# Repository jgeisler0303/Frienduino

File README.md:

# The Frienduino
The Frienduino is an Arduino clone you can make for a friend once you have any kind of Arduino and some soldering skill.
The board is easy to make (single sided) and easy to solder (only through hole components).
It has everything to get started yet it is cheap and simple because it saves on stuff the novice doesn't need (separate power supply and 3.3V regulator).

IMHO, what made the Arduino so popular is its USB connectivity. This lowers the entry barrier to near zero.
No messing around with programmers, no legacy serial port required.
Alas, most of the many many Arduino clones out there lack this key feature.
I guess the reason for this is that, until now, all USB to serial adapters were not available as a through hole component, 
thus discouraging the novice to build a "true to the spirit" clone on their own.

It may seem odd at first to use a programmable micro controller just as a dumb USB to serial converter, but if you look at the price tag and consider it's the only way to get USB to serial as a through hole part it makes a lot of sense to me.
And not to me alone. The folks over at UNL Maker Club must have had a similar reasoning when they chose the 16F1454 as the USB adapter for their [Innovation Board](http://make.unl.edu/innovation-board/), an all SMD Arduino clone.

## Usage
Windows users will find the driver .inf file in this repository. If you connect your ready to use (firmware flashed) Frienduino to a USB port and Windows refuses to identify it as a virtual COM port, go the hardware section of your system configuration and manually update the driver. When asked for the new dirver file point to the inf file supplied in the repository.

Linux users should have no problem. The driver should be automatically installed. But maybe you will have trouble using the serial port created by the driver. In this case you will have to run the Arduino IDE as root or better create a rule to allow ordinary users to use the port (TODO: add link to advice on creating a USB rule file).

## Design
The schematic and PCB are a copy of the [Arduino Duemilanove](http://arduino.cc/en/pmwiki.php?n=Main/arduinoBoardDuemilanove) reference design modified to be a single sided layout using the 16F1454 as the USB adapter and striped off the external power supply. Reset button and ICSP header were moved for better accessability and less complicated routing respectively.

## Making
If you intend to have the Frienduino PCB made, there now is a ready to use gerber file in the repository. If you want the PCBs made by [http://www.seeedstudio.com](http://www.seeedstudio.com) you can even uses this [ready to order project](http://www.seeedstudio.com/service/WmUiIGK1).

For German hackers I have prepared a public [reichelt](http://www.reichelt.de/) shopping cart with all the parts needed [here](https://secure.reichelt.de/index.html?&ACTION=20&AWKID=1013176&PROVID=2084). It totals to 7.78EUR.

## Flashing the PIC 16F1454
The pre-compiled firmware to turn the PIC 16F1454 into a serial adapter can be downloaded from [this](https://github.com/jgeisler0303/PIC16F1454_USB2Serial) repository. To flash the .hex-file to the PIC you can use a second Arduino board and some jumper cables using the soft- and firmware from [this](https://github.com/jgeisler0303/ardpicprog) repository. With this special version of [the original programmer](http://rweather.github.com/ardpicprog/) you can program your PIC in low voltage mode removing the need for a 9V programming voltage and making programming the PIC as simple as programming the atmega.

To flash the PIC, you first have to flash a second, ready for use Arduino (or Frienduino) with the special PIC-flashing firmware found in the repo's "ProgramPIC" folder. Then you have to compile the flashing host program in the "host" folder by typing `make` in the console (this is assuming you have gcc resp. MinGW installed).
Then you have to connect
* pin 5 of the PICs ICSP header to digital pin  4 of your programmer Arduino
* pin 4 of the PICs ICSP header to digital pin  7 of your programmer Arduino
* pin 1 of the PICs 5x1 ICSP header to analog pin  1 of your programmer Arduino
* pin 2 of the PICs ICSP header to +5V of your programmer Arduino
* pin 3 of the PICs ICSP header to ground of your programmer Arduino

Then you have to run `./ardpicprog -p /dev/ttyACM0 --erase --burn --input-hexfile  PIC16F1454_USB2Serial.hex` in Linux, or `ardpicprog.exe -p COM1 --erase --burn --input-hexfile  PIC16F1454_USB2Serial.hex` in Windows in a console in the flashing program's folder (assuming you copied the firmware hex file to this folder, and that the second Arduino is connected to the /dev/ttyACM0 resp. COM1 port). The flashing program will then identify your PIC as a 16F1454, erase it and then burn the new firmware (this will take a while). When the flashing program finishes you're done and can disconnect all jumper cables before you move on to flash the Atmega.

## Flashing the Atmega
In order to make our Atmega Arduino-compatible you have to flash it with an Arduino bootloader. To do this, you can use a second Arduino board and follow these [instructions](http://arduino.cc/en/Tutorial/ArduinoISP). In the Arduino IDE you have to choose "Arduino as ISP" for the programmer and "Arduino Duemilanove w/ Atmega328" as the board.

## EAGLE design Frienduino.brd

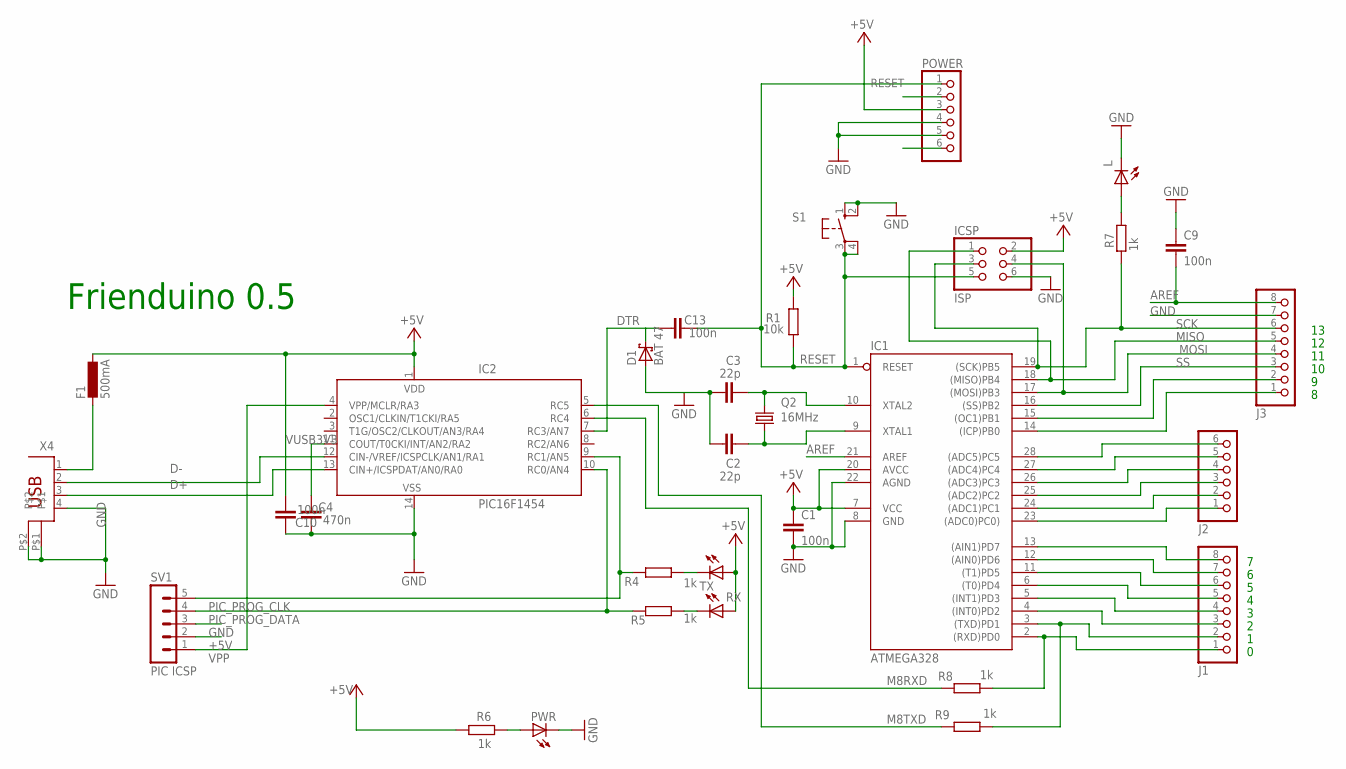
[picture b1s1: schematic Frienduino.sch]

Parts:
C1, C9, C10, C13: 100n; C050-025X075
C2, C3: 22p; C050-024X044
C4: 470n; C050-025X075
D1: BAT 47; DO35-7
F1: 500mA; 0204/5
IC1: ATMEGA328; DIL28-3
IC2: PIC16F1454; DIL14
ICSP: ISP; 2X03
J1, J3: PINHD-1X8; 1X08
J2: PINHD-1X6; 1X06
L: LED3MM
POWER: PINHD-1X6; 1X06
PWR: LED3MM
Q2: 16MHz; HC49/S
R1: 10k; 0204/7
R4, R5, R6, R7, R8, R9: 1k; 0204/7
RX: LED3MM
S1: 10-XX; B3F-10XX
SV1: PIC ICSP; MA05-1
TX: LED3MM
X4: PN61729

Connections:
+5V: C1.1, C10.1, F1.1, IC1.7 (VCC), IC1.20 (AVCC), IC2.1 (VDD), ICSP.2, POWER.3, R1.2, R6.1, RX.A, SV1.2, TX.A
AREF: C9.2, IC1.21 (AREF), J3.8
D+: IC2.13 (CIN+/ICSPDAT/AN0/RA0), X4.3
D-: IC2.12 (CIN-/VREF/ICSPCLK/AN1/RA1), X4.2
DTR: C13.1, D1.C, IC2.7 (RC3/AN7)
GND: C1.2, C2.1, C3.1, C4.1, C9.1, C10.2, D1.A, IC1.8 (GND), IC1.22 (AGND), IC2.14 (VSS), ICSP.6, J3.7, L.K (C), POWER.4, POWER.5, PWR.K (C), S1.1 (S), S1.2 (S1), SV1.3, X4.4, X4.P$1, X4.P$2
M8RXD: IC2.6 (RC4), R8.2
M8TXD: IC2.5 (RC5), R9.2
MISO: IC1.18 ((MISO)PB4), ICSP.1, J3.5
MOSI: IC1.17 ((MOSI)PB3), ICSP.4, J3.4
unnamed: L.A, R7.1
unnamed: PWR.A, R6.2
unnamed: R4.2, TX.K (C)
unnamed: IC1.14 ((ICP)PB0), J3.1
unnamed: C2.2, IC1.9 (XTAL1), Q2.1
unnamed: C3.2, IC1.10 (XTAL2), Q2.2
unnamed: F1.2, X4.1
unnamed: R5.2, RX.K (C)
unnamed: IC1.4 ((INT0)PD2), J1.3
unnamed: IC1.5 ((INT1)PD3), J1.4
unnamed: IC1.6 ((T0)PD4), J1.5
unnamed: IC1.11 ((T1)PD5), J1.6
unnamed: IC1.12 ((AIN0)PD6), J1.7
unnamed: IC1.13 ((AIN1)PD7), J1.8
unnamed: IC1.23 ((ADC0)PC0)), J2.1
unnamed: IC1.24 ((ADC1)PC1), J2.2
unnamed: IC1.25 ((ADC2)PC2), J2.3
unnamed: IC1.26 ((ADC3)PC3), J2.4
unnamed: IC1.27 ((ADC4)PC4), J2.5
unnamed: IC1.28 ((ADC5)PC5), J2.6
unnamed: IC1.15 ((OC1)PB1), J3.2
NC@1: POWER.2
NC@2: POWER.6
PD0: IC1.2 ((RXD)PD0), J1.1, R8.1
PD1: IC1.3 ((TXD)PD1), J1.2, R9.1
PIC_PROG_CLK: IC2.9 (RC1/AN5), R4.1, SV1.5
PIC_PROG_DATA: IC2.10 (RC0/AN4), R5.1, SV1.4
RESET: C13.2, IC1.1 (RESET), ICSP.5, POWER.1, R1.1, S1.3, S1.4 (P1)
SCK: IC1.19 ((SCK)PB5), ICSP.3, J3.6, R7.2
SS: IC1.16 ((SS)PB2), J3.3
VPP: IC2.4 (VPP/MCLR/RA3), SV1.1
VUSB3V3: C4.2, IC2.11 (COUT/T0CKI/INT/AN2/RA2)

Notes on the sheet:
Frienduino 0.5

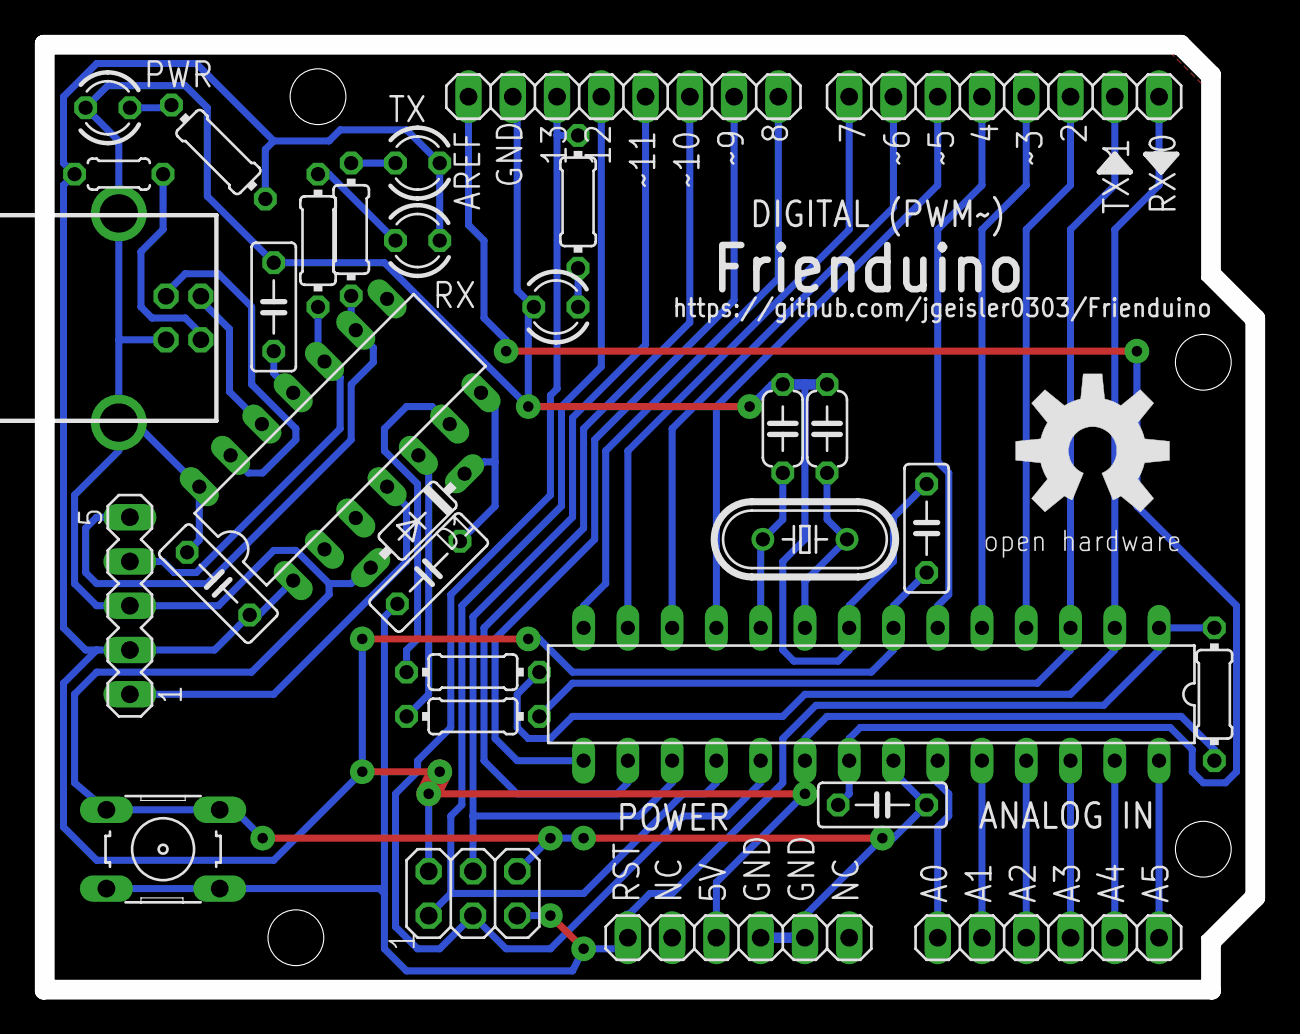
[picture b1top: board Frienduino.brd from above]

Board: 2 copper layers, 69.6 x 54.4 mm, 31 parts (0 on the bottom side), 40 nets.

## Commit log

2015-01-17 Update README.md
    added reichelt shopping cart link to README
2015-01-17 Update README.md
    added price of reichelt shopping cart
2015-01-18 changed resistors to 7mm raster
2015-06-01 prepared board for manufacture and added gergers
2015-06-06 added Windows driver -inf file. changed README to new low voltage programming mode of ardpicprog
2015-06-06 changed README to mention the gerbers and seeedstudio prject
